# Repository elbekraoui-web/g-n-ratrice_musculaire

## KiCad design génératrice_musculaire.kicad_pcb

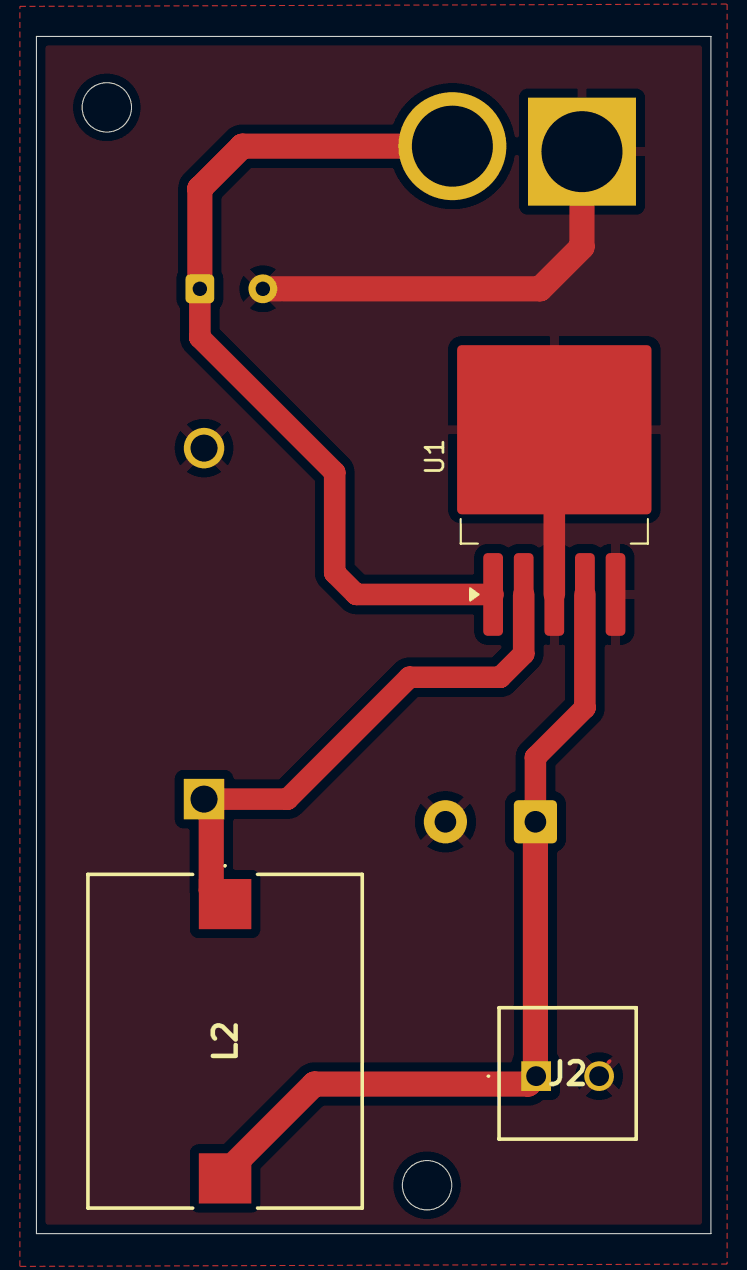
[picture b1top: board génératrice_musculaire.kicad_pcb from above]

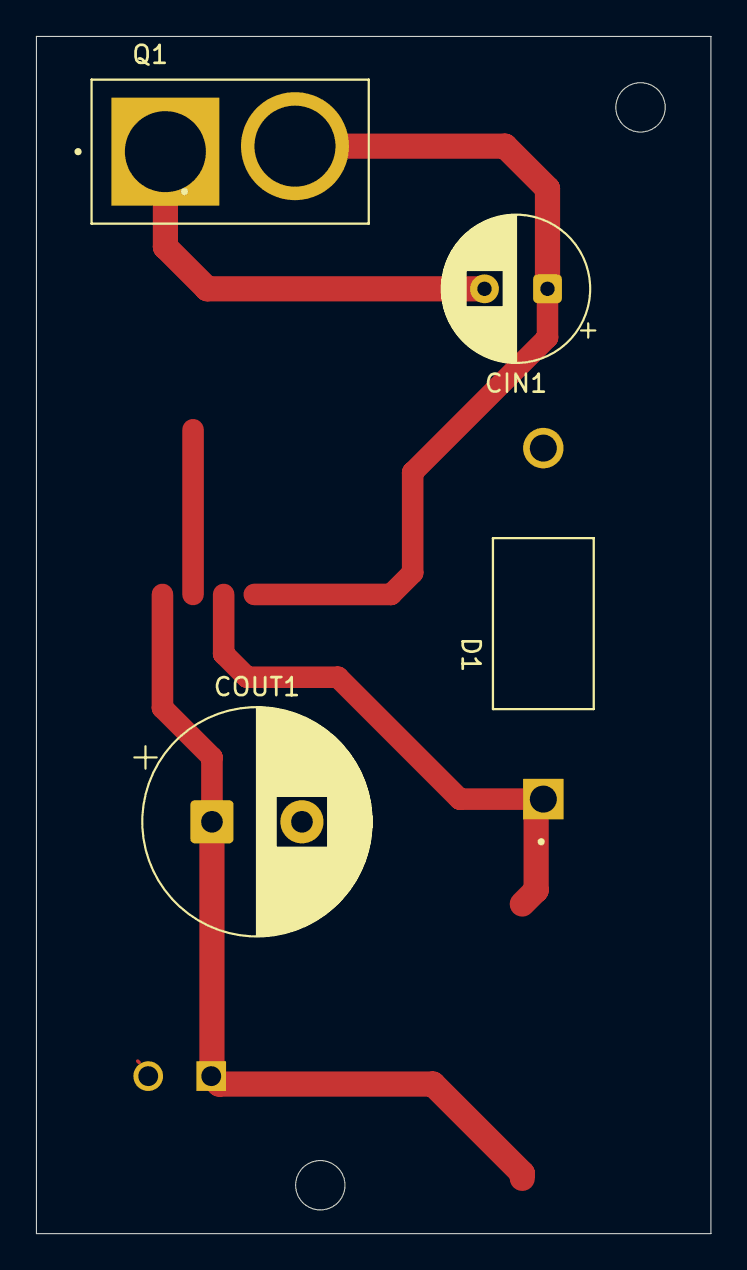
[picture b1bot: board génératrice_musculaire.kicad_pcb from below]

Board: 2 copper layers, 37.5 x 66.5 mm, 7 parts (4 on the bottom side), 4 nets.

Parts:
CIN1: 100µF; CP_Radial_D8.0mm_P3.50mm
COUT1: 1000µF; CP_Radial_D12.5mm_P5.00mm
D1: MBR360; DIOAD1950W125L950D560
J2: CTB0308_2; CTB03082
L2: MP002808
Q1: XT60_YELLOW; AMASS_XT60PB-M
U1: LM2576HVS-12; TO-263-5_TabPin3

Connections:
GND: CIN1.2, COUT1.2, D1.2 (A), J2.2, Q1.1, U1.3 (GND), U1.5 (~ON/OFF)
unnamed: D1.1 (K), L2.1, U1.2 (OUT)
unnamed: COUT1.1, J2.1, L2.2, U1.4 (FB)
unnamed: CIN1.1, Q1.2, U1.1 (VIN)
